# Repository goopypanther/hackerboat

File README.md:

Hackerboat Control Software
===========================
The hackerbot labs autonomous hackerboat is a modified kayak with 900MHz/2.4GHz radios, electric motor, IMU, scientific sensors & solar power rechargeable batteries.

The control system uses a beaglebone & arduino mega which communicate using REST with a land based host computer.

Embedded Software
-----------------

 * Beaglebone
  * REST communication with host PC
  * IMU/GPS tracking & waypoint navigation
  * MAVLink-over-UART communication with arduino
 * Arduino
  * Motor control
  * Magnetic navigation
  * Ship health & sensor feedback

See [./embedded_software](https://github.com/JeremyRuhland/hackerboat/tree/master/embedded_software)

Doxygen documentation of beaglebone software may be generated with `make doxy` in the `./embedded_software/beaglebone` folder and found at `./embedded_software/beaglebone/doc`.

Host Software
-------------
Javascript served by the Beaglebone. Coming soon...

Hardware Schematics
-------------------
On-ship hardware for connecting beaglebone, arduino and power systems together.

See [./hardware](https://github.com/JeremyRuhland/hackerboat/tree/master/hardware)

Boat System Documentation
-------------------------
View under [./doc](https://github.com/JeremyRuhland/hackerboat/tree/master/doc)

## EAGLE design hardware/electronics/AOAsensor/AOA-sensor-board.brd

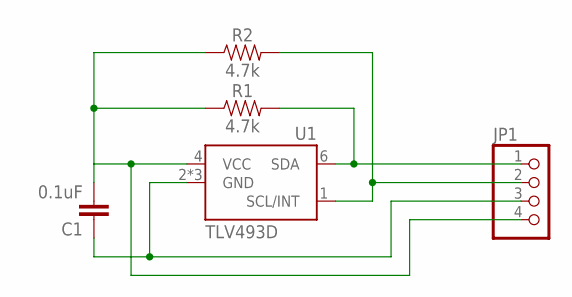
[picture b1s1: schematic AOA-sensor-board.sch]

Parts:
C1: 0.1uF; 0603
JP1: PINHD-1X4; 1X04
R1, R2: 4.7k; 0603
U1: TLV493D; TSOP-6

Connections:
GND: C1.1, JP1.3, U1.2 (GND), U1.3 (GND), U1.5 (GND)
SCL: JP1.2, R2.2, U1.1 (SCL/INT)
SDA: JP1.1, R1.2, U1.6 (SDA)
VCC: C1.2, JP1.4, R1.1, R2.1, U1.4 (VCC)

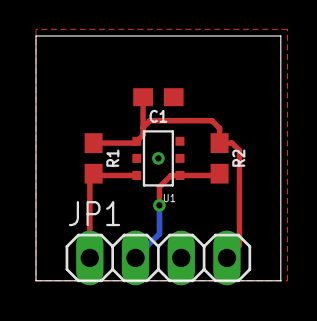
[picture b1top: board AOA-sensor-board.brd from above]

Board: 2 copper layers, 13.6 x 13.6 mm, 5 parts (0 on the bottom side), 4 nets.

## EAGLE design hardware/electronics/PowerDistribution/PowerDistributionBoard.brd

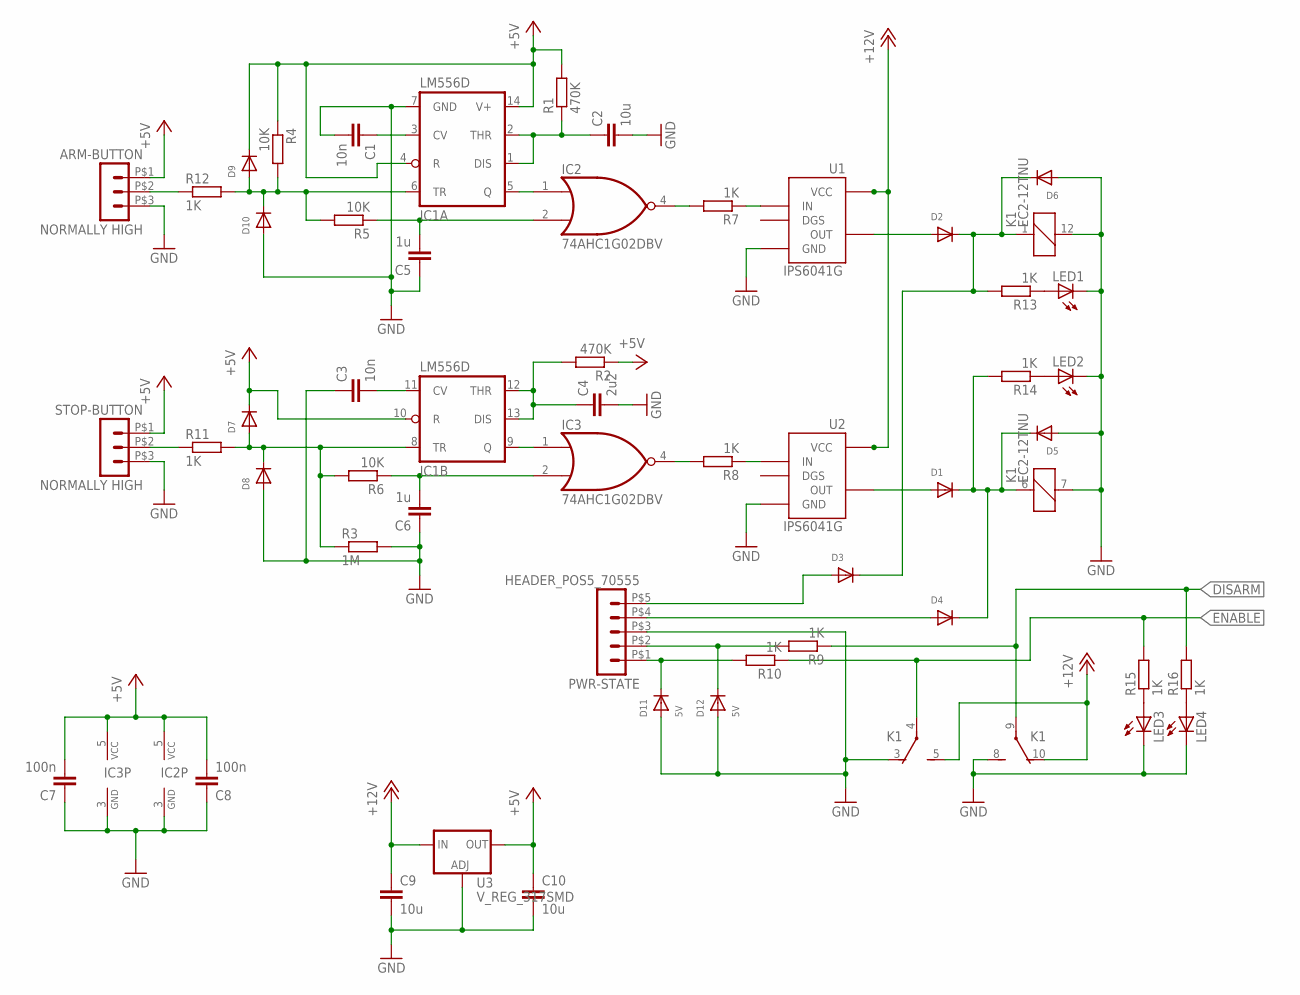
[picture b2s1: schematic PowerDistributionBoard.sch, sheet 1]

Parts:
ARM-BUTTON: NORMALLY HIGH; 70555-POS3; PARTNO 0705550037
C1, C3: 10n; C0603; PARTNO CL10B103KB8NCNC
C2: 10u; C0603; PARTNO C1608JB1E106M080AC
C4: 2u2; C0603; PARTNO TMK107ABJ225KA-T
C5, C6: 1u; C0603; PARTNO UMK107BJ105KA-T
C7, C8: 100n; C0603; PARTNO CC0603ZRY5V9BB104
C9, C10: 10u; C1206; PARTNO C3216X5R1E106M
D1, D2, D3, D4, D5, D6, D7, D8, D9, D10: DIODESOD-123; SOD-123; PARTNO CDBW140-G
D11, D12: 5V; SOD-123; PARTNO SMF5.0A
IC1: LM556D; SO14; PARTNO LM556CM
IC2, IC3: 74AHC1G02DBV; SOT23-5; PARTNO SN74AHC1G02DBVR
K1: EC2-12TNU; EC2-*TNU; PARTNO EC2-12TNU
LED1, LED2, LED3, LED4: LEDCHIP-LED0805; CHIP-LED0805; PARTNO LG R971-KN-1
PWR-STATE: HEADER_POS5_70555; 70555-POS5; PARTNO 0705550039
R1, R2: 470K; R0603; PARTNO MCR03FZPEJ474
R3: 1M; R0603; PARTNO MCT06030C1004FP500
R4, R5, R6: 10K; R0603; PARTNO RMCF0603FT10K0
R7, R8, R9, R10, R11, R12, R13, R14, R15, R16: 1K; R0603; PARTNO RMCF0603FT1K00
STOP-BUTTON: NORMALLY HIGH; 70555-POS3; PARTNO 0705550037
U1, U2: IPS6041G; SO08; PARTNO IPS6041GPBF
U3: V_REG_317SMD; SOT223; PARTNO NCP1117ST50T3G

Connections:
+5V: ARM-BUTTON.P$1 (1), C7.2, C8.2, C10.1, D7.C, D9.C, IC1.4 (R), IC1.10 (R), IC1.14 (V+), IC2.5 (VCC), IC3.5 (VCC), R1.2, R2.1, R4.1, STOP-BUTTON.P$1 (1), U3.2 (OUT)
+12V: C9.1, K1.5 (S), K1.10 (O), U1.5 (VCC), U1.6 (VCC), U1.7 (VCC), U1.8 (VCC), U2.5 (VCC), U2.6 (VCC), U2.7 (VCC), U2.8 (VCC), U3.3 (IN); also elsewhere on the board
DISARM: K1.9, R9.1, R16.2
ENABLE: K1.4, R10.1, R15.2; also elsewhere on the board
GND: ARM-BUTTON.P$3 (3), C1.2, C2.2, C3.1, C4.2, C5.1, C6.1, C7.1, C8.1, C9.2, C10.2, D5.A, D6.A, D8.A, D10.A, D11.A, D12.A, IC1.7 (GND), IC2.3 (GND), IC3.3 (GND), K1.3 (O), K1.7 (2), K1.8 (S), K1.12 (2), LED1.C, LED2.C, LED3.C, LED4.C, PWR-STATE.P$3 (3), R3.2, STOP-BUTTON.P$3 (3), U1.1 (GND), U2.1 (GND), U3.1 (ADJ); also elsewhere on the board
unnamed: C5.2, IC2.2 (I1), R5.1
unnamed: C1.1, IC1.3 (CV)
unnamed: C6.2, IC3.2 (I1), R6.1
unnamed: C2.1, IC1.1 (DIS), IC1.2 (THR), R1.1
unnamed: C4.1, IC1.12 (THR), IC1.13 (DIS), R2.2
unnamed: IC2.4 (O), R7.2
unnamed: IC1.5 (Q), IC2.1 (I0)
unnamed: D9.A, D10.C, IC1.6 (TR), R4.2, R5.2, R12.2
unnamed: C3.2, IC1.11 (CV)
unnamed: IC3.4 (O), R8.2
unnamed: IC1.9 (Q), IC3.1 (I0)
unnamed: D7.A, D8.C, IC1.8 (TR), R3.1, R6.2, R11.2
unnamed: R7.1, U1.2 (IN)
unnamed: R8.1, U2.2 (IN)
unnamed: D4.A, PWR-STATE.P$4 (4)
unnamed: D3.A, PWR-STATE.P$5 (5)
unnamed: D1.A, U2.4 (OUT)
unnamed: D2.A, U1.4 (OUT)
unnamed: D2.C, D3.C, D6.C, K1.1, R13.2
unnamed: D1.C, D4.C, D5.C, K1.6 (1), R14.2
unnamed: LED2.A, R14.1
unnamed: LED1.A, R13.1
unnamed: D12.C, PWR-STATE.P$2 (2), R9.2
unnamed: D11.C, PWR-STATE.P$1 (1), R10.2
unnamed: ARM-BUTTON.P$2 (2), R12.1
unnamed: R11.1, STOP-BUTTON.P$2 (2)
unnamed: LED3.A, R15.1
unnamed: LED4.A, R16.1

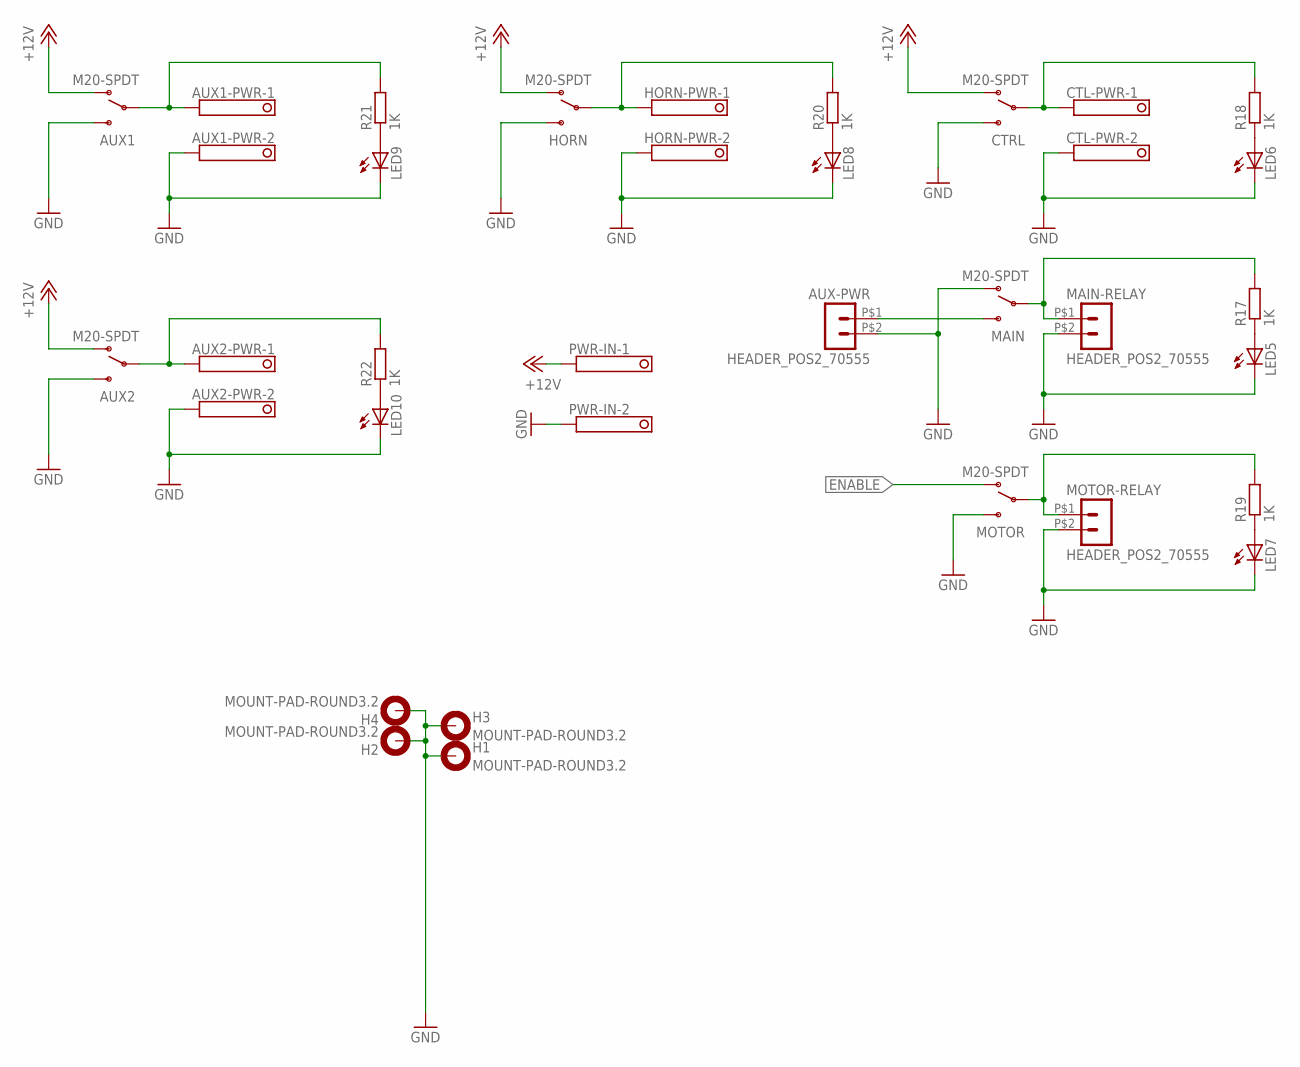
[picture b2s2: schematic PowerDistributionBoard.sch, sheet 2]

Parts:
AUX1, AUX2: M20-SPDT; PARTNO M2012LL1W01
AUX1-PWR, AUX2-PWR: 1751248; PARTNO 1751248
AUX-PWR: HEADER_POS2_70555; 70555-POS2; PARTNO 0705550036
CTL-PWR: 1751248; PARTNO 1751248
CTRL: M20-SPDT; PARTNO M2012LL1W01
H1, H2, H3, H4: MOUNT-PAD-ROUND3.2; 3,2-PAD
HORN: M20-SPDT; PARTNO M2012LL1W01
HORN-PWR: 1751248; PARTNO 1751248
LED5, LED6, LED7, LED8, LED9, LED10: LEDCHIP-LED0805; CHIP-LED0805; PARTNO LG R971-KN-1
MAIN: M20-SPDT; PARTNO M2012LL1W01
MAIN-RELAY: HEADER_POS2_70555; 70555-POS2; PARTNO 0705550036
MOTOR: M20-SPDT; PARTNO M2012LL1W01
MOTOR-RELAY: HEADER_POS2_70555; 70555-POS2; PARTNO 0705550036
PWR-IN: 1751248; PARTNO 1751248
R17, R18, R19, R20, R21, R22: 1K; R0603; PARTNO RMCF0603FT1K00

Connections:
+12V: AUX1.1 (O), AUX2.1 (O), CTRL.1 (O), HORN.1 (O), PWR-IN.1; also elsewhere on the board
ENABLE: MOTOR.1 (O); also elsewhere on the board
GND: AUX1.3 (S), AUX1-PWR.2, AUX2.3 (S), AUX2-PWR.2, AUX-PWR.P$2 (2), CTL-PWR.2, CTRL.3 (S), H1.B3,2, H2.B3,2, H3.B3,2, H4.B3,2, HORN.3 (S), HORN-PWR.2, LED5.C, LED6.C, LED7.C, LED8.C, LED9.C, LED10.C, MAIN.1 (O), MAIN-RELAY.P$2 (2), MOTOR.3 (S), MOTOR-RELAY.P$2 (2), PWR-IN.2; also elsewhere on the board
unnamed: AUX1.2, AUX1-PWR.1, R21.2
unnamed: LED6.A, R18.1
unnamed: LED9.A, R21.1
unnamed: LED5.A, R17.1
unnamed: HORN.2, HORN-PWR.1, R20.2
unnamed: AUX-PWR.P$1 (1), MAIN.3 (S)
unnamed: LED7.A, R19.1
unnamed: MOTOR.2, MOTOR-RELAY.P$1 (1), R19.2
unnamed: AUX2.2, AUX2-PWR.1, R22.2
unnamed: CTL-PWR.1, CTRL.2, R18.2
unnamed: LED10.A, R22.1
unnamed: LED8.A, R20.1
unnamed: MAIN.2, MAIN-RELAY.P$1 (1), R17.2

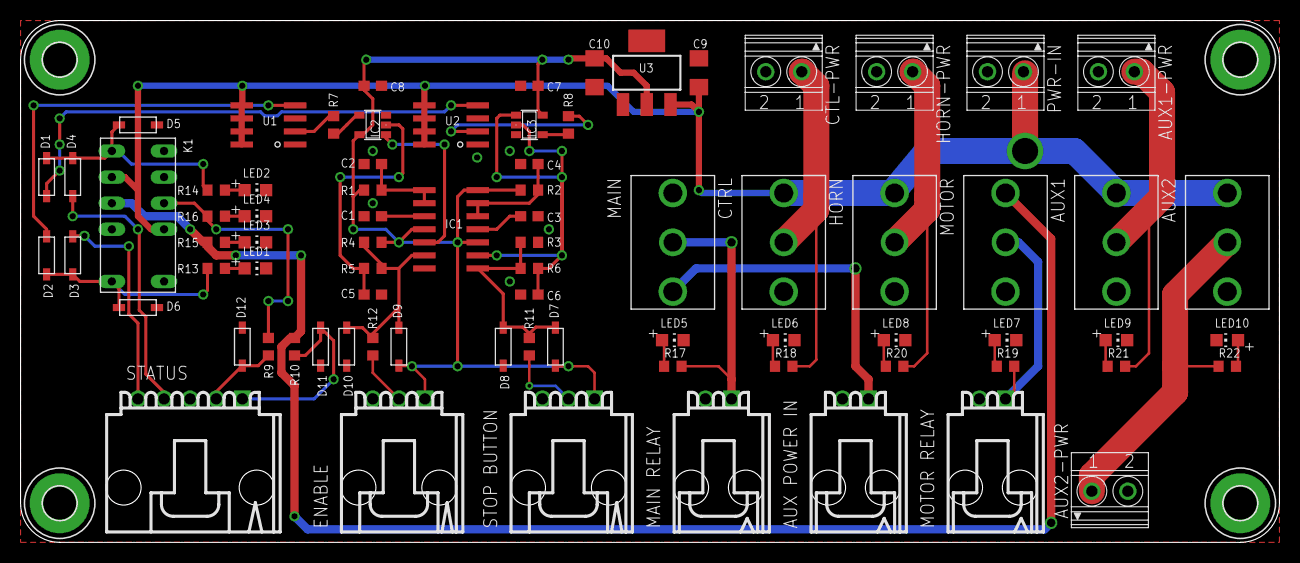
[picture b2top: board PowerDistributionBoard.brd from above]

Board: 2 copper layers, 122.6 x 50.8 mm, 82 parts (0 on the bottom side), 46 nets.

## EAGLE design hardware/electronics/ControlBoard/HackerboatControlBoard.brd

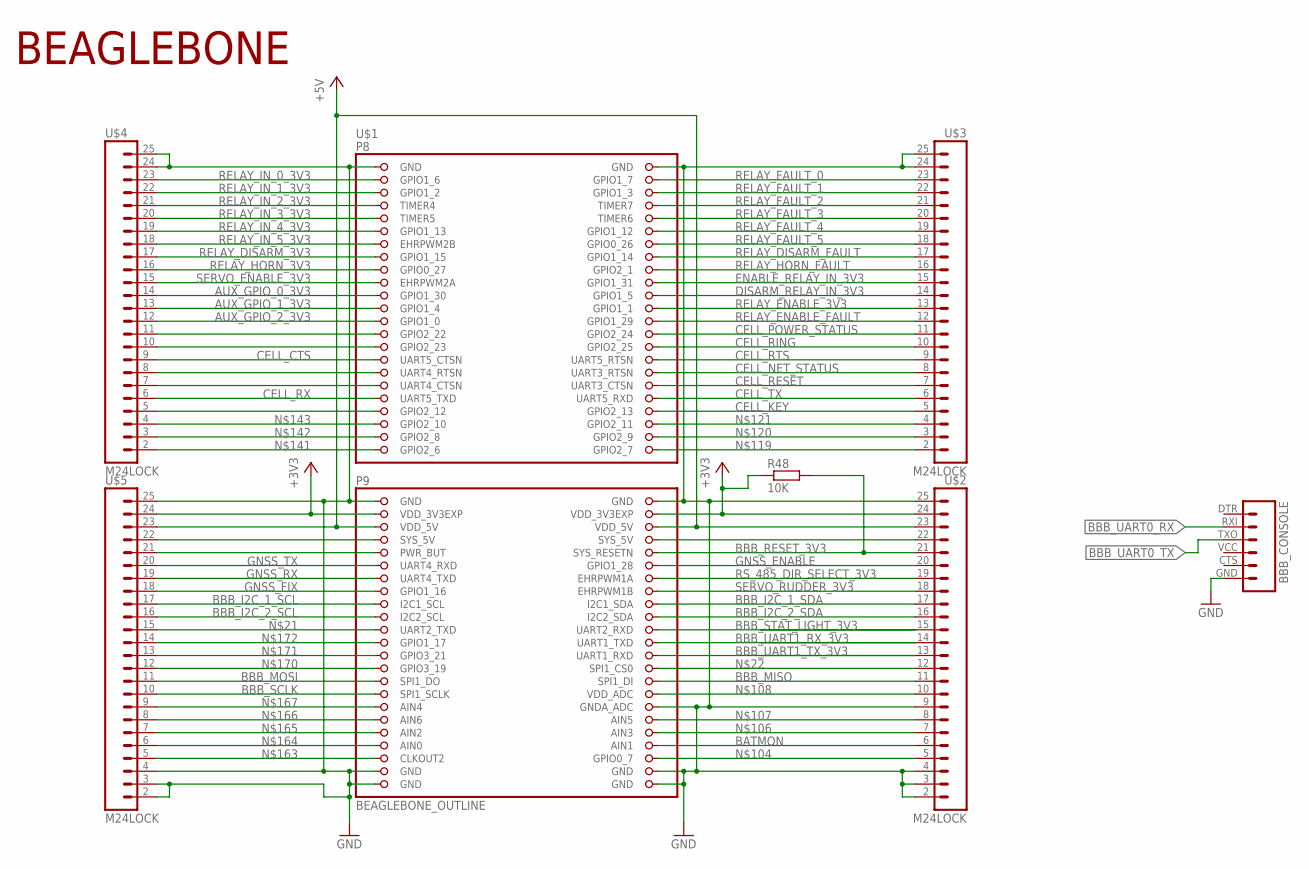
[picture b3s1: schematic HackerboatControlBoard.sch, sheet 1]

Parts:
BBB_CONSOLE: FTDI_BASICPTH; FTDI_BASIC; PARTNO 215299-6
R48: 10K; R0603; PARTNO RNCP0603FTD10K0
U$1: BEAGLEBONE_OUTLINE; BEAGLEBONE_SHIELD; PARTNO ?
U$2, U$3, U$4, U$5: M24LOCK; 1X24_LOCK; PARTNO *

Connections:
+3V3: R48.1, U$1.49 (VDD_3V3EXP), U$1.50 (VDD_3V3EXP), U$2.24, U$5.24; also elsewhere on the board
+5V: U$1.51 (VDD_5V), U$1.52 (VDD_5V), U$2.23, U$5.23; also elsewhere on the board
AUX_GPIO_0_3V3: U$1.21 (GPIO1_30), U$4.14; also elsewhere on the board
AUX_GPIO_1_3V3: U$1.23 (GPIO1_4), U$4.13; also elsewhere on the board
AUX_GPIO_2_3V3: U$1.25 (GPIO1_0), U$4.12; also elsewhere on the board
BATMON: U$1.86 (AIN1), U$2.6; also elsewhere on the board
BBB_I2C_1_SCL: U$1.63 (I2C1_SCL), U$5.17; also elsewhere on the board
BBB_I2C_1_SDA: U$1.64 (I2C1_SDA), U$2.17; also elsewhere on the board
BBB_I2C_2_SCL: U$1.65 (I2C2_SCL), U$5.16; also elsewhere on the board
BBB_I2C_2_SDA: U$1.66 (I2C2_SDA), U$2.16; also elsewhere on the board
BBB_MISO: U$1.76 (SPI1_DI), U$2.11; also elsewhere on the board
BBB_MOSI: U$1.75 (SPI1_DO), U$5.11; also elsewhere on the board
BBB_RESET_3V3: R48.2, U$1.56 (SYS_RESETN), U$2.21; also elsewhere on the board
BBB_SCLK: U$1.77 (SPI1_SCLK), U$5.10; also elsewhere on the board
BBB_STAT_LIGHT_3V3: U$1.68 (UART2_RXD), U$2.15
BBB_UART0_RX: BBB_CONSOLE.RXI (2); also elsewhere on the board
BBB_UART0_TX: BBB_CONSOLE.TXO (3); also elsewhere on the board
BBB_UART1_RX_3V3: U$1.70 (UART1_TXD), U$2.14; also elsewhere on the board
BBB_UART1_TX_3V3: U$1.72 (UART1_RXD), U$2.13; also elsewhere on the board
CELL_CTS: U$1.31 (UART5_CTSN), U$4.9; also elsewhere on the board
CELL_KEY: U$1.40 (GPIO2_13), U$3.5; also elsewhere on the board
CELL_NET_STATUS: U$1.34 (UART3_RTSN), U$3.8; also elsewhere on the board
CELL_POWER_STATUS: U$1.28 (GPIO2_24), U$3.11; also elsewhere on the board
CELL_RESET: U$1.36 (UART3_CTSN), U$3.7; also elsewhere on the board
CELL_RING: U$1.30 (GPIO2_25), U$3.10; also elsewhere on the board
CELL_RTS: U$1.32 (UART5_RTSN), U$3.9; also elsewhere on the board
CELL_RX: U$1.37 (UART5_TXD), U$4.6; also elsewhere on the board
CELL_TX: U$1.38 (UART5_RXD), U$3.6; also elsewhere on the board
DISARM_RELAY_IN_3V3: U$1.22 (GPIO1_5), U$3.14; also elsewhere on the board
ENABLE_RELAY_IN_3V3: U$1.20 (GPIO1_31), U$3.15; also elsewhere on the board
GND: BBB_CONSOLE.GND (6), U$1.1 (GND), U$1.2 (GND), U$1.47 (GND), U$1.48 (GND), U$1.80 (GNDA_ADC), U$1.89 (GND), U$1.90 (GND), U$1.91 (GND), U$1.92 (GND), U$2.2, U$2.3, U$2.4, U$2.9, U$2.25, U$3.24, U$3.25, U$4.24, U$4.25, U$5.2, U$5.3, U$5.4, U$5.25; also elsewhere on the board
GNSS_ENABLE: U$1.58 (GPIO1_28), U$2.20; also elsewhere on the board
GNSS_FIX: U$1.61 (GPIO1_16), U$5.18; also elsewhere on the board
GNSS_RX: U$1.59 (UART4_TXD), U$5.19; also elsewhere on the board
GNSS_TX: U$1.57 (UART4_RXD), U$5.20; also elsewhere on the board
unnamed: U$1.67 (UART2_TXD), U$5.15
unnamed: U$1.74 (SPI1_CS0), U$2.12
unnamed: U$1.27 (GPIO2_22), U$4.11
unnamed: U$1.29 (GPIO2_23), U$4.10
unnamed: U$1.33 (UART4_RTSN), U$4.8
unnamed: U$1.35 (UART4_CTSN), U$4.7
unnamed: U$1.39 (GPIO2_12), U$4.5
unnamed: U$1.88 (GPIO0_7), U$2.5
unnamed: U$1.84 (AIN3), U$2.7
unnamed: U$1.82 (AIN5), U$2.8
unnamed: U$1.78 (VDD_ADC), U$2.10
unnamed: U$1.54 (SYS_5V), U$2.22
unnamed: U$1.46 (GPIO2_7), U$3.2
unnamed: U$1.44 (GPIO2_9), U$3.3
unnamed: U$1.42 (GPIO2_11), U$3.4
unnamed: U$1.45 (GPIO2_6), U$4.2
unnamed: U$1.43 (GPIO2_8), U$4.3
unnamed: U$1.41 (GPIO2_10), U$4.4
unnamed: U$1.87 (CLKOUT2), U$5.5
unnamed: U$1.85 (AIN0), U$5.6
unnamed: U$1.83 (AIN2), U$5.7
unnamed: U$1.81 (AIN6), U$5.8
unnamed: U$1.79 (AIN4), U$5.9
unnamed: U$1.73 (GPIO3_19), U$5.12
unnamed: U$1.71 (GPIO3_21), U$5.13
unnamed: U$1.69 (GPIO1_17), U$5.14
unnamed: U$1.55 (PWR_BUT), U$5.21
RELAY_DISARM_3V3: U$1.15 (GPIO1_15), U$4.17; also elsewhere on the board
RELAY_DISARM_FAULT: U$1.16 (GPIO1_14), U$3.17; also elsewhere on the board
RELAY_ENABLE_3V3: U$1.24 (GPIO1_1), U$3.13; also elsewhere on the board
RELAY_ENABLE_FAULT: U$1.26 (GPIO1_29), U$3.12; also elsewhere on the board
RELAY_FAULT_0: U$1.4 (GPIO1_7), U$3.23; also elsewhere on the board
RELAY_FAULT_1: U$1.6 (GPIO1_3), U$3.22; also elsewhere on the board
RELAY_FAULT_2: U$1.8 (TIMER7), U$3.21; also elsewhere on the board
RELAY_FAULT_3: U$1.10 (TIMER6), U$3.20; also elsewhere on the board
RELAY_FAULT_4: U$1.12 (GPIO1_12), U$3.19; also elsewhere on the board
RELAY_FAULT_5: U$1.14 (GPIO0_26), U$3.18; also elsewhere on the board
RELAY_HORN_3V3: U$1.17 (GPIO0_27), U$4.16; also elsewhere on the board
RELAY_HORN_FAULT: U$1.18 (GPIO2_1), U$3.16; also elsewhere on the board
RELAY_IN_0_3V3: U$1.3 (GPIO1_6), U$4.23; also elsewhere on the board
RELAY_IN_1_3V3: U$1.5 (GPIO1_2), U$4.22; also elsewhere on the board
RELAY_IN_2_3V3: U$1.7 (TIMER4), U$4.21; also elsewhere on the board
RELAY_IN_3_3V3: U$1.9 (TIMER5), U$4.20; also elsewhere on the board
RELAY_IN_4_3V3: U$1.11 (GPIO1_13), U$4.19; also elsewhere on the board
RELAY_IN_5_3V3: U$1.13 (EHRPWM2B), U$4.18; also elsewhere on the board
RS_485_DIR_SELECT_3V3: U$1.60 (EHRPWM1A), U$2.19; also elsewhere on the board
SERVO_ENABLE_3V3: U$1.19 (EHRPWM2A), U$4.15; also elsewhere on the board
SERVO_RUDDER_3V3: U$1.62 (EHRPWM1B), U$2.18; also elsewhere on the board
SYS_5V: U$1.53 (SYS_5V), U$5.22

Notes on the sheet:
BEAGLEBONE

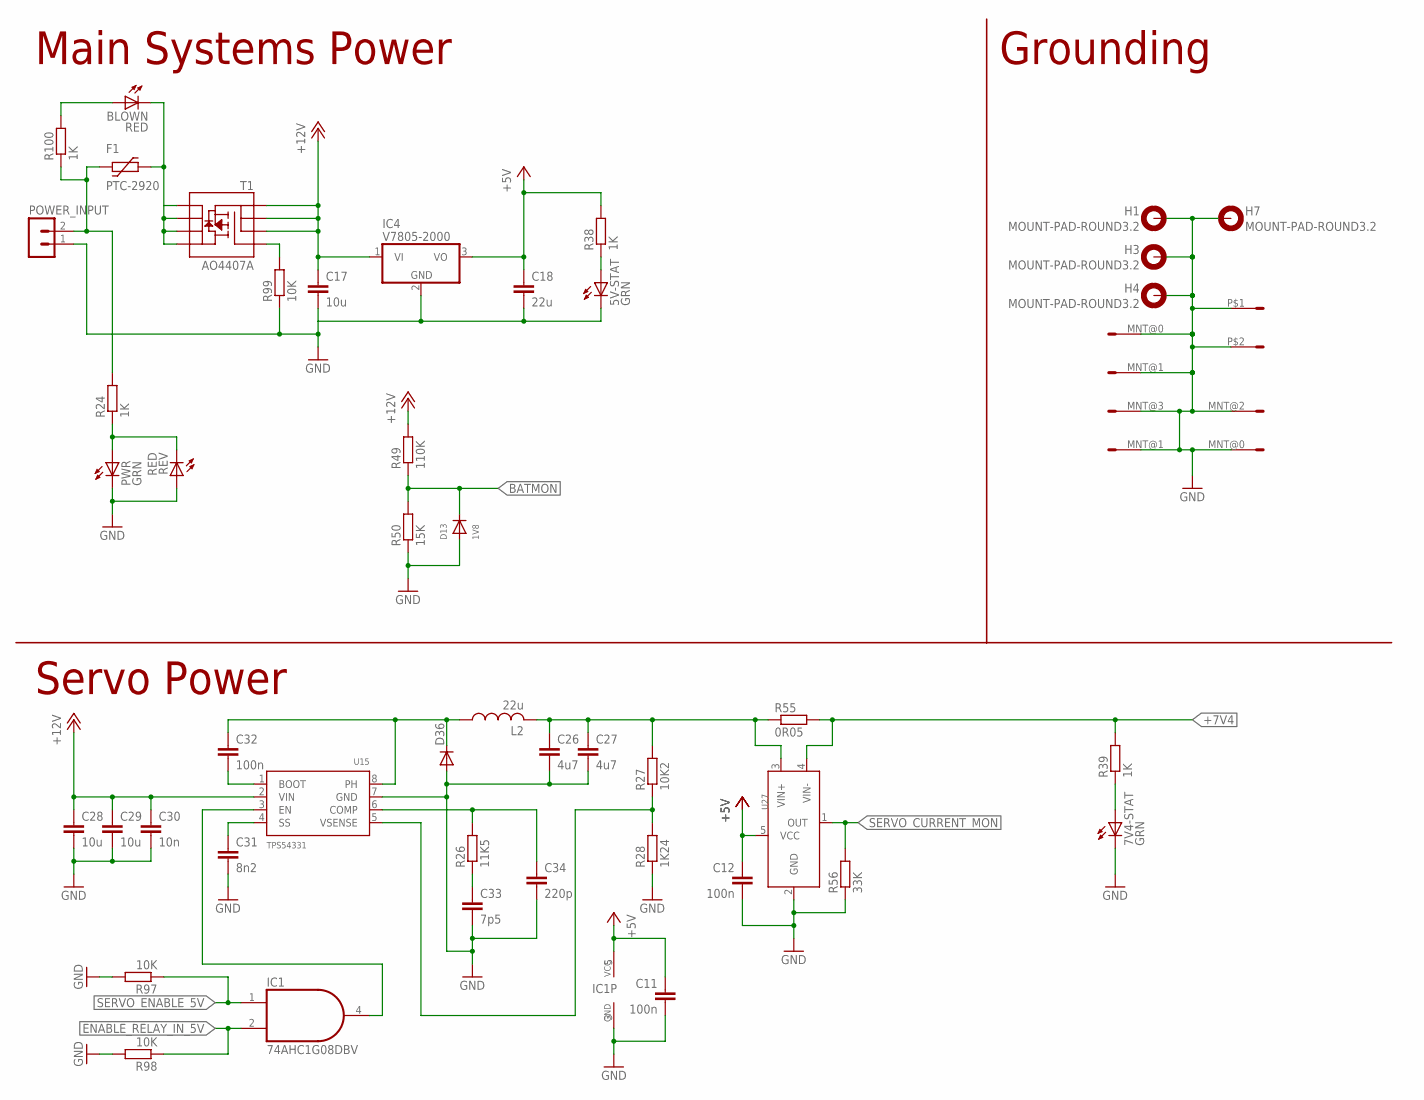
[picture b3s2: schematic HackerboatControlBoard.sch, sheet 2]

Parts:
5V-STAT, 7V4-STAT: GRN; CHIPLED_0805; PARTNO LG R971-KN-1
BLOWN: RED; CHIPLED_0805; PARTNO LH R974-LP-1
C11, C12, C32: 100n; C0603; PARTNO CC0603KRX7R9BB104
C17, C28, C29: 10u; C1210; PARTNO UMK325BJ106MM
C18: 22u; C1210; PARTNO GRM32ER61E226KE15K
C26, C27: 4u7; C1210; PARTNO UMK325F475ZH
C30: 10n; C0603; PARTNO CL10B103KB8NCNC
C31: 8n2; C0603; PARTNO CL10B822KB8SFNC
C33: 7p5; C0603; PARTNO CL10C7R5DB8NNNC
C34: 220p; C0603; PARTNO CL10B221KC8WPNC
CELL: FONA; FONA-3G; PARTNO BCS-118-L-S-TE
D13: 1V8; SOD-123; PARTNO MMSZ4678-TP
D36: SPARKFUN_DIODESMA; SPARKFUN_SMA-DIODE; PARTNO SK310A-LTP
F1: PTC-2920; 2920L; PARTNO MF-LSMF300/24X-2
GPS: ULTIMATE-GPS; PARTNO BCS-109-L-S-TE
H1, H3, H4, H7: MOUNT-PAD-ROUND3.2; 3,2-PAD; PARTNO ?
IC1: 74AHC1G08DBV; SOT23-5; PARTNO MC74HC1G08DTT1G
IC4: V7805-2000; TO220V; PARTNO V7805-2000
IMU: 9-DOF-BREAKOUT; PARTNO BCS-110-L-S-TE
L2: 22u; NR60XX; PARTNO NR6045T220M
POWER_INPUT: 3-1437664-0; CONN-2; PARTNO NC6-P108-02
PWR: GRN; CHIPLED_0805; PARTNO LG R971-KN-1
R24, R38, R39, R100: 1K; R0603; PARTNO RMCF0603FT1K00
R26: 11K5; R0603; PARTNO RC0603FR-0711K5L
R27: 10K2; R0603; PARTNO RC0603FR-0710K2L
R28: 1K24; R0603; PARTNO RC0603FR-071K24L
R49: 110K; R0603; PARTNO RC0603JR-07110KL
R50: 15K; R0603; PARTNO RC0603JR-0715KL
R55: 0R05; R2512; PARTNO PE2512FKE070R05L
R56: 33K; R0603; PARTNO ERJ-3EKF3302V
R97, R98, R99: 10K; R0603; PARTNO RNCP0603FTD10K0
REV: RED; CHIPLED_0805; PARTNO LH R974-LP-1
T1: AO4407A; SO08; PARTNO AO4407A
U15: TPS54331; SO08; PARTNO TPS54331DR
U27: INA169; SOT23-5L; PARTNO INA169NA/3K

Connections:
+5V: C11.1, C12.1, C18.1, IC1.5 (VCC), IC4.3 (VO), R38.2, U27.5 (VCC); also elsewhere on the board
+7V4: R39.2, R55.2, U27.4 (VIN-); also elsewhere on the board
+7V4_OUT: C26.1, C27.1, L2.2, R27.2, R55.1, U27.3 (VIN+)
+12V: C17.1, C28.1, C29.1, C30.1, IC4.1 (VI), R49.2, T1.1 (S), T1.2 (S), T1.3 (S), U15.2 (VIN); also elsewhere on the board
BATMON: D13.C, R49.1, R50.2; also elsewhere on the board
ENABLE_RELAY_IN_5V: IC1.2 (I1), R98.1; also elsewhere on the board
GND: 5V-STAT.C, 7V4-STAT.C, C11.2, C12.2, C17.2, C18.2, C26.2, C27.2, C28.2, C29.2, C30.2, C31.2, C33.2, C34.2, CELL.P$1 (9), CELL.P$2 (9), D13.A, D36.A, GPS.MNT@0 (9), GPS.MNT@1 (9), H1.B3,2, H3.B3,2, H4.B3,2, H7.B3,2, IC1.3 (GND), IC4.2 (GND), IMU.MNT@0 (9), IMU.MNT@1 (9), IMU.MNT@2 (9), IMU.MNT@3 (9), POWER_INPUT.1, PWR.C, R28.1, R50.1, R56.1, R97.2, R98.2, R99.1, REV.A, U15.7 (GND), U27.2 (GND); also elsewhere on the board
unnamed: IC1.4 (O), U15.3 (EN)
unnamed: C31.1, U15.4 (SS)
unnamed: C32.2, U15.1 (BOOT)
unnamed: C32.1, D36.C, L2.1, U15.8 (PH)
unnamed: C33.1, R26.1
unnamed: C34.1, R26.2, U15.6 (COMP)
unnamed: R27.1, R28.2, U15.5 (VSENSE)
unnamed: BLOWN.C, F1.P$2 (2), T1.5 (D), T1.6 (D), T1.7 (D), T1.8 (D)
unnamed: R99.2, T1.4 (G)
unnamed: F1.P$1 (1), POWER_INPUT.2, R24.2, R100.1
unnamed: BLOWN.A, R100.2
unnamed: PWR.A, R24.1, REV.C
unnamed: 5V-STAT.A, R38.1
unnamed: 7V4-STAT.A, R39.1
SERVO_CURRENT_MON: R56.2, U27.1 (OUT); also elsewhere on the board
SERVO_ENABLE_5V: IC1.1 (I0), R97.1; also elsewhere on the board

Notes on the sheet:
Main Systems Power
Servo Power
Grounding

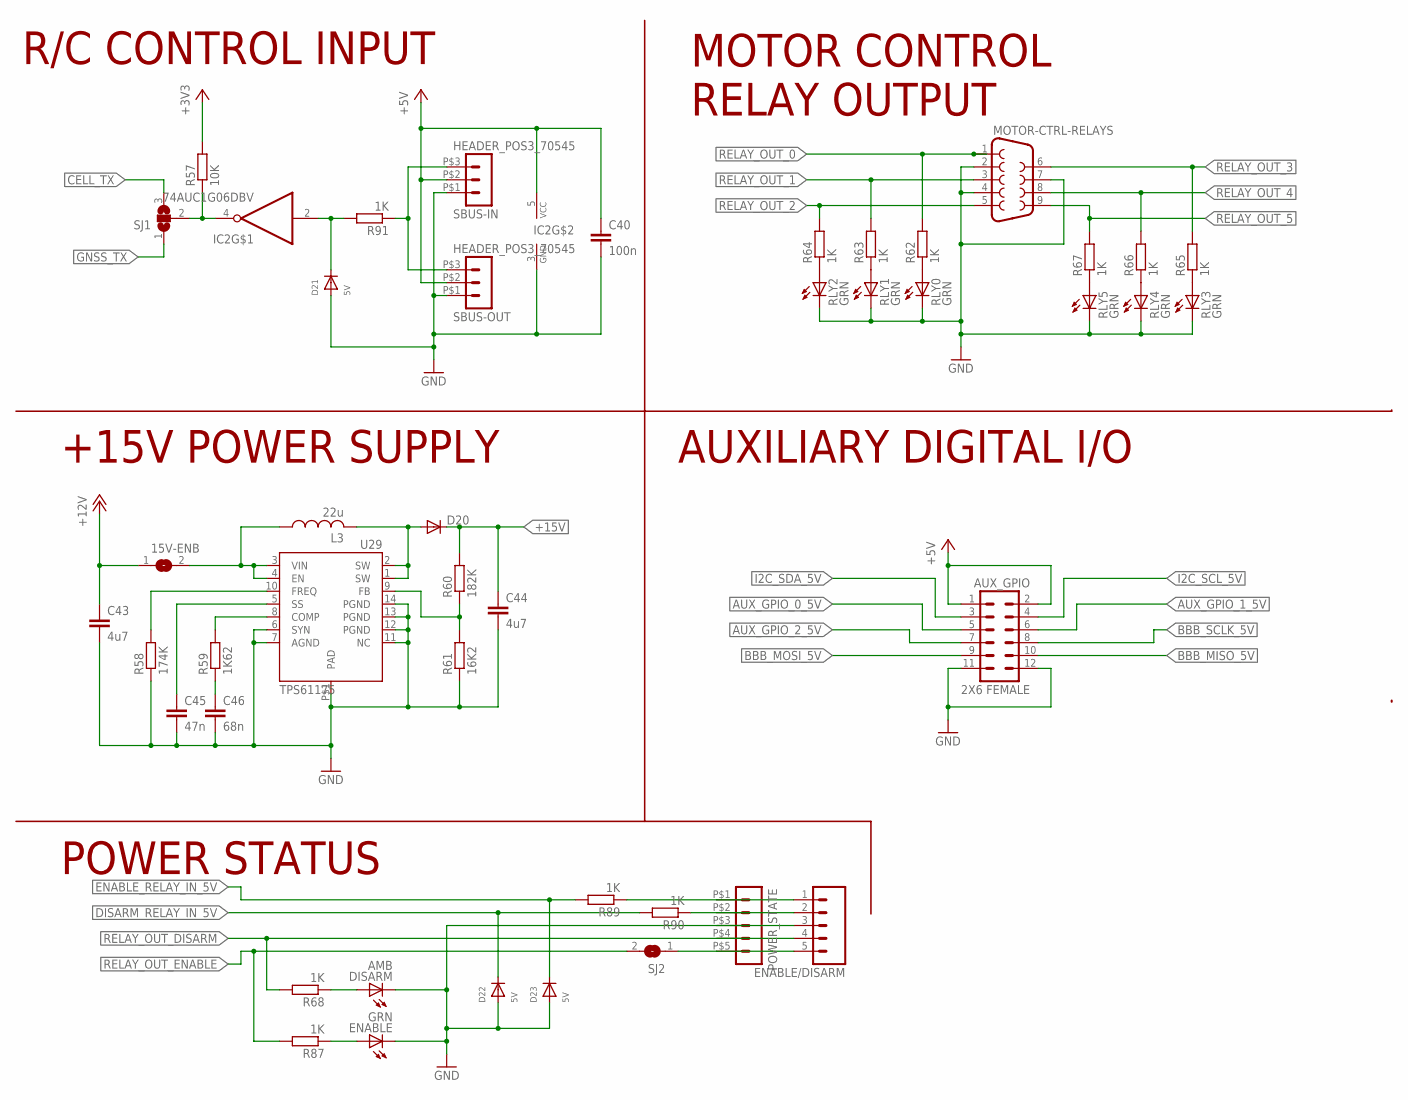
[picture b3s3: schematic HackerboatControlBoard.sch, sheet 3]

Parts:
15V-ENB: SJ; PARTNO ?
AUX_GPIO: 2X6 FEMALE; 2X6; PARTNO *
C40: 100n; C0603; PARTNO CC0603KRX7R9BB104
C43, C44: 4u7; C1210; PARTNO UMK325F475ZH
C45: 47n; C0603; PARTNO C1608X7R1H473M
C46: 68n; C0603; PARTNO CL10C680JB8NNNC
D20: SPARKFUN_DIODESMA; SPARKFUN_SMA-DIODE; PARTNO SK310A-LTP
D21, D22, D23: 5V; SOD-123; PARTNO SMF5.0A
DISARM: AMB; CHIPLED_0805; PARTNO HSMA-C170
ENABLE: GRN; CHIPLED_0805; PARTNO LG R971-KN-1
ENABLE/DISARM: M05LOCK; 1X05_LOCK; PARTNO *
IC2: 74AUC1G06DBV; SOT23-5; PARTNO SN74LVC1G06DBVR
L3: 22u; SRN8040; PARTNO SRN8040-220M
MOTOR-CTRL-RELAYS: DB9FEMALE; DB9; PARTNO 1734354-1
POWER_STATE: HEADER_POS5_70555; 70555-POS5; PARTNO 0705550039
R57: 10K; R0603; PARTNO RNCP0603FTD10K0
R58: 174K; R0603; PARTNO RC0603FR-07174KL
R59: 1K62; R0603; PARTNO RC0603FR-071K62L
R60: 182K; R0603; PARTNO ERJ-3EKF1823V
R61: 16K2; R0603; PARTNO RC0603FR-0716K2L
R62, R63, R64, R65, R66, R67, R68, R87, R89, R90, R91: 1K; R0603; PARTNO RMCF0603FT1K00
RLY0, RLY1, RLY2, RLY3, RLY4, RLY5: GRN; CHIPLED_0805; PARTNO LG R971-KN-1
SBUS-IN: HEADER_POS3_70545; 70545-POS3; PARTNO 0705450037
SBUS-OUT: HEADER_POS3_70545; 70545-POS3; PARTNO 0705450037
SJ1: SJ2W; SJ_2; PARTNO ?
SJ2: SJ; PARTNO *
U29: TPS61175; HTSSOP14; PARTNO TPS61175PWPR

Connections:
+3V3: R57.2; also elsewhere on the board
+5V: AUX_GPIO.1, AUX_GPIO.2, C40.1, IC2.5 (VCC), SBUS-IN.P$2 (2), SBUS-OUT.P$2 (2); also elsewhere on the board
+12V: 15V-ENB.1, C43.1; also elsewhere on the board
+15V: C44.1, D20.C, R60.2; also elsewhere on the board
AUX_GPIO_0_5V: AUX_GPIO.5; also elsewhere on the board
AUX_GPIO_1_5V: AUX_GPIO.6; also elsewhere on the board
AUX_GPIO_2_5V: AUX_GPIO.7; also elsewhere on the board
BBB_MISO_5V: AUX_GPIO.10; also elsewhere on the board
BBB_MOSI_5V: AUX_GPIO.9; also elsewhere on the board
BBB_SCLK_5V: AUX_GPIO.8; also elsewhere on the board
CELL_TX: SJ1.3; also elsewhere on the board
DISARM_RELAY_IN_5V: D22.C, R90.2; also elsewhere on the board
ENABLE_RELAY_IN_5V: D23.C, R89.2; also elsewhere on the board
GND: AUX_GPIO.11, AUX_GPIO.12, C40.2, C43.2, C44.2, C45.2, C46.2, D21.A, D22.A, D23.A, DISARM.C, ENABLE.C, ENABLE/DISARM.3, IC2.3 (GND), MOTOR-CTRL-RELAYS.2, MOTOR-CTRL-RELAYS.4, MOTOR-CTRL-RELAYS.7, POWER_STATE.P$3 (3), R58.1, R61.1, RLY0.C, RLY1.C, RLY2.C, RLY3.C, RLY4.C, RLY5.C, SBUS-IN.P$1 (1), SBUS-OUT.P$1 (1), U29.6 (SYN), U29.7 (AGND), U29.11 (NC), U29.12 (PGND), U29.13 (PGND), U29.14 (PGND), U29.P$1 (PAD); also elsewhere on the board
GNSS_TX: SJ1.1; also elsewhere on the board
I2C_SCL_5V: AUX_GPIO.4; also elsewhere on the board
I2C_SDA_5V: AUX_GPIO.3; also elsewhere on the board
unnamed: D21.C, IC2.2 (I), R91.2
unnamed: IC2.4 (O), R57.1, SJ1.2
unnamed: R62.1, RLY0.A
unnamed: R63.1, RLY1.A
unnamed: R64.1, RLY2.A
unnamed: DISARM.A, R68.1
unnamed: R65.1, RLY3.A
unnamed: R66.1, RLY4.A
unnamed: R67.1, RLY5.A
unnamed: ENABLE.A, R87.1
unnamed: C46.1, R59.1
unnamed: R59.2, U29.8 (COMP)
unnamed: C45.1, U29.5 (SS)
unnamed: R58.2, U29.10 (FREQ)
unnamed: D20.A, L3.2, U29.1 (SW), U29.2 (SW)
unnamed: R60.1, R61.2, U29.9 (FB)
unnamed: ENABLE/DISARM.1, POWER_STATE.P$1 (1), R89.1
unnamed: ENABLE/DISARM.2, POWER_STATE.P$2 (2), R90.1
unnamed: 15V-ENB.2, L3.1, U29.3 (VIN), U29.4 (EN)
unnamed: ENABLE/DISARM.5, POWER_STATE.P$5 (5), SJ2.1
RELAY_OUT_0: MOTOR-CTRL-RELAYS.1, R62.2; also elsewhere on the board
RELAY_OUT_1: MOTOR-CTRL-RELAYS.3, R63.2; also elsewhere on the board
RELAY_OUT_2: MOTOR-CTRL-RELAYS.5, R64.2; also elsewhere on the board
RELAY_OUT_3: MOTOR-CTRL-RELAYS.6, R65.2; also elsewhere on the board
RELAY_OUT_4: MOTOR-CTRL-RELAYS.8, R66.2; also elsewhere on the board
RELAY_OUT_5: MOTOR-CTRL-RELAYS.9, R67.2; also elsewhere on the board
RELAY_OUT_DISARM: ENABLE/DISARM.4, POWER_STATE.P$4 (4), R68.2; also elsewhere on the board
RELAY_OUT_ENABLE: R87.2, SJ2.2; also elsewhere on the board
SBUS_IN_5V: R91.1, SBUS-IN.P$3 (3), SBUS-OUT.P$3 (3)

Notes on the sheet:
R/C CONTROL INPUT
+15V POWER SUPPLY
MOTOR CONTROL RELAY OUTPUT
AUXILIARY DIGITAL I/O
POWER STATUS

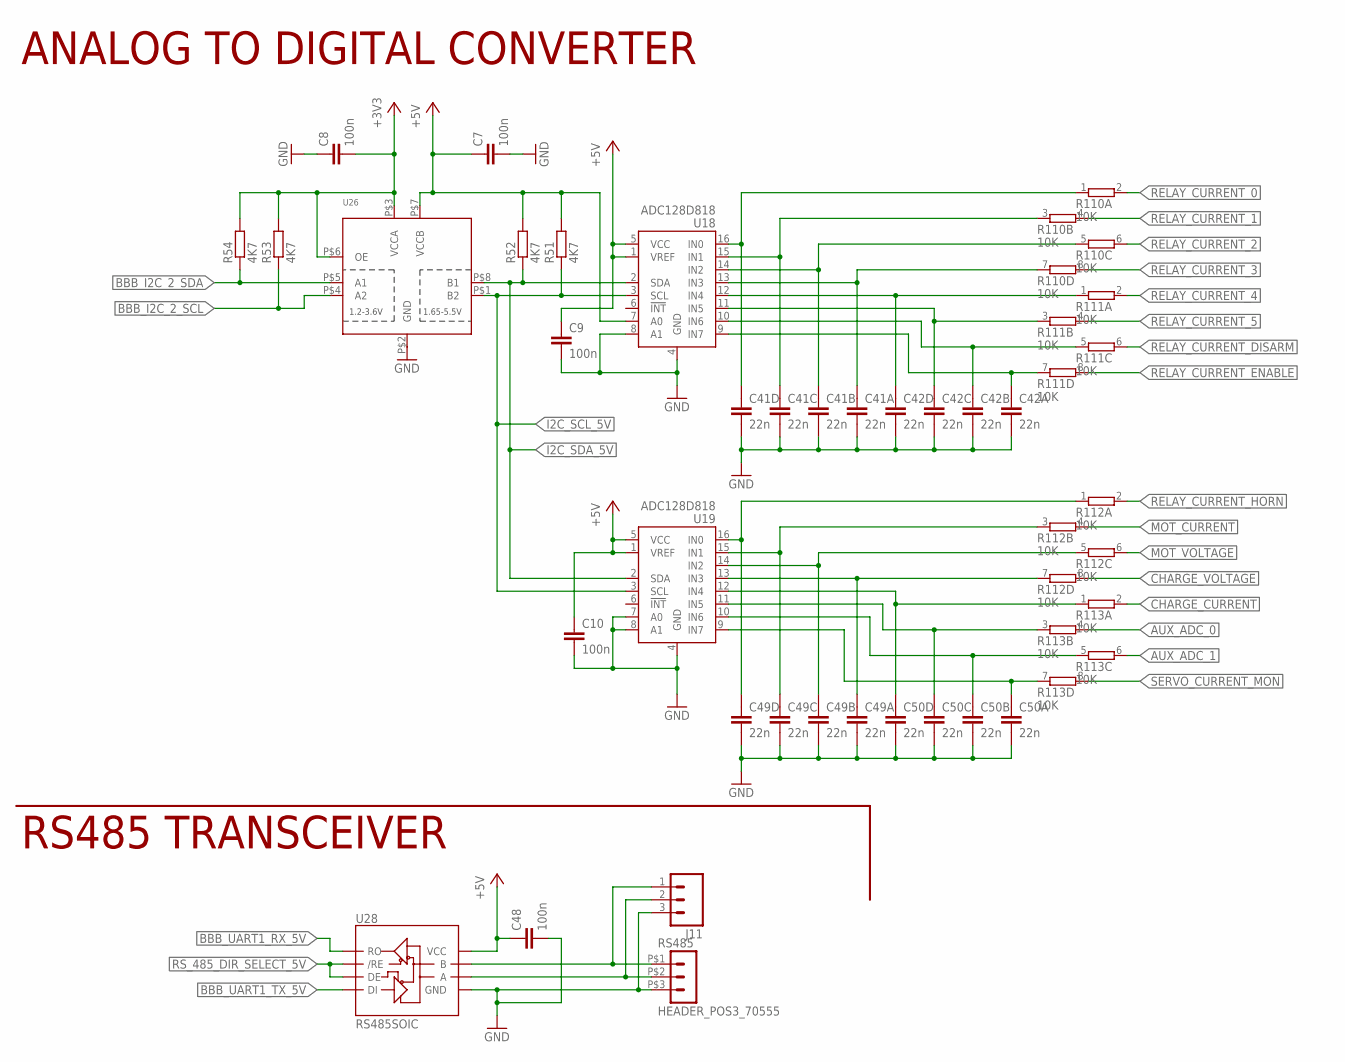
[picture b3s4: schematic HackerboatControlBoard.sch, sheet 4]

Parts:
C7, C8, C9, C10, C48: 100n; C0603; PARTNO CC0603KRX7R9BB104
C41, C42, C49, C50: 22n; 0805X4-CAP; PARTNO CKCL44X5R1C223M085AA
J11: M03LOCK; 1X03_LOCK; PARTNO ?
R51, R52, R53, R54: 4K7; R0603; PARTNO RC1608J472CS
R110, R111, R112, R113: 10K; CTS742C083-RES; PARTNO 742C083103JPTR
RS485: HEADER_POS3_70555; 70555-POS3; PARTNO 0705550037
U18, U19: ADC128D818; TSSOP16; PARTNO ADC128D818CIMTX
U26: TXS0102; VFSOP-8; PARTNO TXS0102DCURG4
U28: RS485SOIC; SO08; PARTNO SN75176BDR

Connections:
+3V3: C8.2, R53.2, R54.2, U26.P$3 (VCCA), U26.P$6 (OE); also elsewhere on the board
+5V: C7.1, C9.1, C10.1, C48.1, R51.2, R52.2, U18.1 (VREF), U18.5 (VCC), U18.7 (A0), U19.1 (VREF), U19.5 (VCC), U26.P$7 (VCCB), U28.8 (VCC); also elsewhere on the board
AUX_ADC_0: R113.4 (2); also elsewhere on the board
AUX_ADC_1: R113.6 (2); also elsewhere on the board
BBB_I2C_2_SCL: R53.1, U26.P$4 (A2); also elsewhere on the board
BBB_I2C_2_SDA: R54.1, U26.P$5 (A1); also elsewhere on the board
BBB_UART1_RX_5V: U28.1 (RO); also elsewhere on the board
BBB_UART1_TX_5V: U28.4 (DI); also elsewhere on the board
CHARGE_CURRENT: R113.2; also elsewhere on the board
CHARGE_VOLTAGE: R112.8 (2); also elsewhere on the board
GND: C7.2, C8.1, C9.2, C10.2, C41.2, C41.4 (2), C41.6 (2), C41.8 (2), C42.2, C42.4 (2), C42.6 (2), C42.8 (2), C48.2, C49.2, C49.4 (2), C49.6 (2), C49.8 (2), C50.2, C50.4 (2), C50.6 (2), C50.8 (2), J11.3, RS485.P$3 (3), U18.4 (GND), U18.8 (A1), U19.4 (GND), U19.7 (A0), U19.8 (A1), U26.P$2 (GND), U28.5 (GND); also elsewhere on the board
I2C_SCL_5V: R51.1, U18.3 (SCL), U19.3 (SCL), U26.P$1 (B2); also elsewhere on the board
I2C_SDA_5V: R52.1, U18.2 (SDA), U19.2 (SDA), U26.P$8 (B1); also elsewhere on the board
MOT_CURRENT: R112.4 (2); also elsewhere on the board
MOT_VOLTAGE: R112.6 (2); also elsewhere on the board
unnamed: J11.1, RS485.P$1 (1), U28.7 (B)
unnamed: J11.2, RS485.P$2 (2), U28.6 (A)
unnamed: C41.7 (1), R110.1, U18.16 (IN0)
unnamed: C41.5 (1), R110.3 (1), U18.15 (IN1)
unnamed: C49.7 (1), R112.1, U19.16 (IN0)
unnamed: C41.3 (1), R110.5 (1), U18.14 (IN2)
unnamed: C41.1, R110.7 (1), U18.13 (IN3)
unnamed: C42.7 (1), R111.1, U18.12 (IN4)
unnamed: C42.5 (1), R111.3 (1), U18.11 (IN5)
unnamed: C42.3 (1), R111.5 (1), U18.10 (IN6)
unnamed: C42.1, R111.7 (1), U18.9 (IN7)
unnamed: C49.5 (1), R112.3 (1), U19.15 (IN1)
unnamed: C49.3 (1), R112.5 (1), U19.14 (IN2)
unnamed: C49.1, R112.7 (1), U19.13 (IN3)
unnamed: C50.7 (1), R113.1, U19.12 (IN4)
unnamed: C50.5 (1), R113.3 (1), U19.11 (IN5)
unnamed: C50.3 (1), R113.5 (1), U19.10 (IN6)
unnamed: C50.1, R113.7 (1), U19.9 (IN7)
RELAY_CURRENT_0: R110.2; also elsewhere on the board
RELAY_CURRENT_1: R110.4 (2); also elsewhere on the board
RELAY_CURRENT_2: R110.6 (2); also elsewhere on the board
RELAY_CURRENT_3: R110.8 (2); also elsewhere on the board
RELAY_CURRENT_4: R111.2; also elsewhere on the board
RELAY_CURRENT_5: R111.4 (2); also elsewhere on the board
RELAY_CURRENT_DISARM: R111.6 (2); also elsewhere on the board
RELAY_CURRENT_ENABLE: R111.8 (2); also elsewhere on the board
RELAY_CURRENT_HORN: R112.2; also elsewhere on the board
RS_485_DIR_SELECT_5V: U28.2 (/RE), U28.3 (DE); also elsewhere on the board
SERVO_CURRENT_MON: R113.8 (2); also elsewhere on the board

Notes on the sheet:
ANALOG TO DIGITAL CONVERTER
RS485 TRANSCEIVER

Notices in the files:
parts and their libraries:
SparkFun-Capacitors: Licensing: Creative Commons ShareAlike 4.0 International - https://creativecommons.org/licenses/by-sa/4.0
hackerbot: (c) Hackerbot Labs 2009. CC-BY 3.0
SparkFun-Boards: Licensing: CC v3.0 Share-Alike You are welcome to use this library for commercial purposes.
